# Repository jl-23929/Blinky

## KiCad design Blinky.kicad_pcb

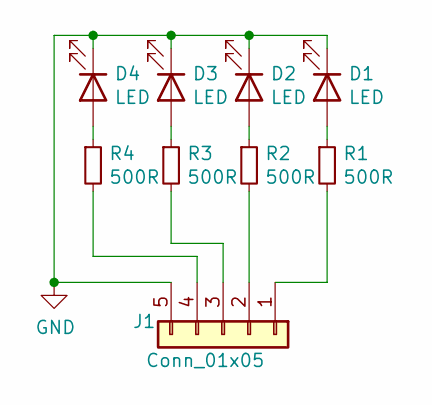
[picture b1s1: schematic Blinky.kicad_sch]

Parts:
D1, D2, D3, D4: LED; LED_D3.0mm
J1: Conn_01x05; PinHeader_1x05_P2.54mm_Vertical
R1, R2, R3, R4: 500R; R_Axial_DIN0309_L9.0mm_D3.2mm_P12.70mm_Horizontal

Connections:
GND: D1.1 (K), D2.1 (K), D3.1 (K), D4.1 (K), J1.5
unnamed: D1.2 (A), R1.1
unnamed: D2.2 (A), R2.1
unnamed: D3.2 (A), R3.1
unnamed: J1.1, R1.2
unnamed: J1.2, R2.2
unnamed: J1.3, R3.2
unnamed: D4.2 (A), R4.1
unnamed: J1.4, R4.2

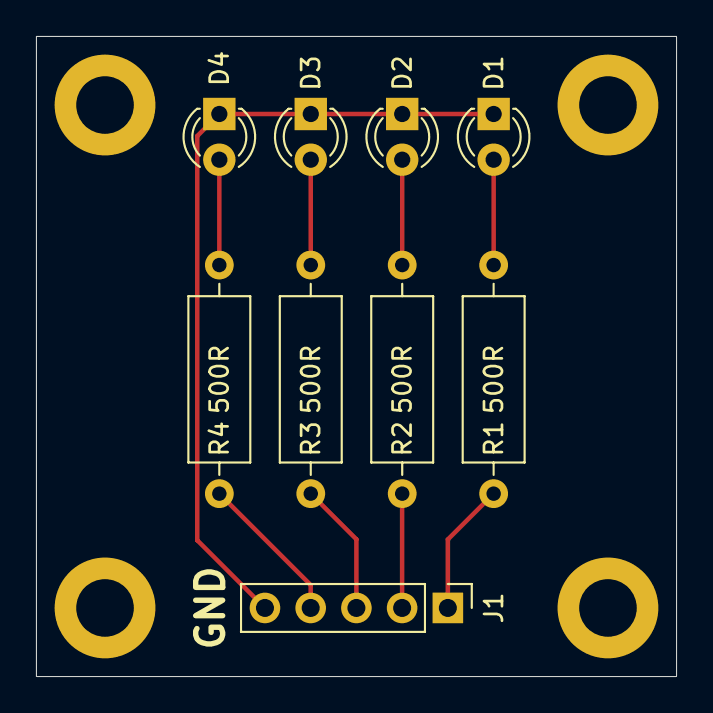
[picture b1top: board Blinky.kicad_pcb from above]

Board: 2 copper layers, 35.6 x 35.6 mm, 9 parts (0 on the bottom side), 9 nets.

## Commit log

2024-07-04 Blinky
2024-07-06 Added Code
